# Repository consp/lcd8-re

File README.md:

# Gui based on lvgl9 for eBikes using a VESC motor controller 

Features:
* customisable (obviously ...)
* Faster update rates than any factory device
* Uses LVGL
* Has MCU with sufficient power and memory to do everything I want it to without too much problems.

## who is this for?

Anyone who wants to build their own eBike display and wants an example. This project is provided as is. No commercial usage is allowed of any kind unless stated explicitly otherwise.

### Who is this not for?

Anyone who expects a ready made product without effort.

## Supported platforms 

- Custom display:
  - Transflective LCD
  - 4 button support
  - Persistent Real time clock (if battery added) 
  - CAN/UART capable
  - Fast
  - Be able to connect to phone to show nav updates (via custom [gadgetbridge app](https://github.com/consp/Gadgetbridge))
  - Connect and use VESC messages ([custom version needed](https://github.com/consp/bldc), [custom tooling needed](https://github.com/consp/vesc-tool))
  - STM32H743
  - Should have enough power to output 1.5A on the 5V rail to USB

## Known issues
Probably many, there is a bug in the PCB making the ADC unreliable when a battery is installed.

# Attribution
Temperature icon: [Temperature Vectors by Vecteezy](https://www.vecteezy.com/free-vector/temperature)
Engine icon: [Heat icons created by HAJICON - Flaticon](https://www.flaticon.com/free-icons/heatv)
Brake icon: [Brake icons created by Smashicons - Flaticon](https://www.flaticon.com/free-icons/brake)
Trip icon: [Trip icons created by improstudio - Flaticon](https://www.flaticon.com/free-icons/trip)
Other icons: [Uicons - Flaticon](https://www.flaticon.com/uicons)
Headlight and headlight auto: [Headlight icons created by TravisAvery - Flaticon](https://www.flaticon.com/free-icon/headlights_9104236)

# License
All stuff not already licenced otherwise is only available under CC-BY-NC-4.0 https://creativecommons.org/licenses/by-nc/4.0/ . For commercial use contact me. No waranty of any kind is provided. No claims of any kind can be made.

# Contribution

If, for some reason, you want to add something or make a pull request: It's fine to do so but don't expect a prompt response. Any LLM based code or other generated files will be rejected without warning.
If, for some reason, you have a question: Use the discussion part of github. Do not expect a prompt response.

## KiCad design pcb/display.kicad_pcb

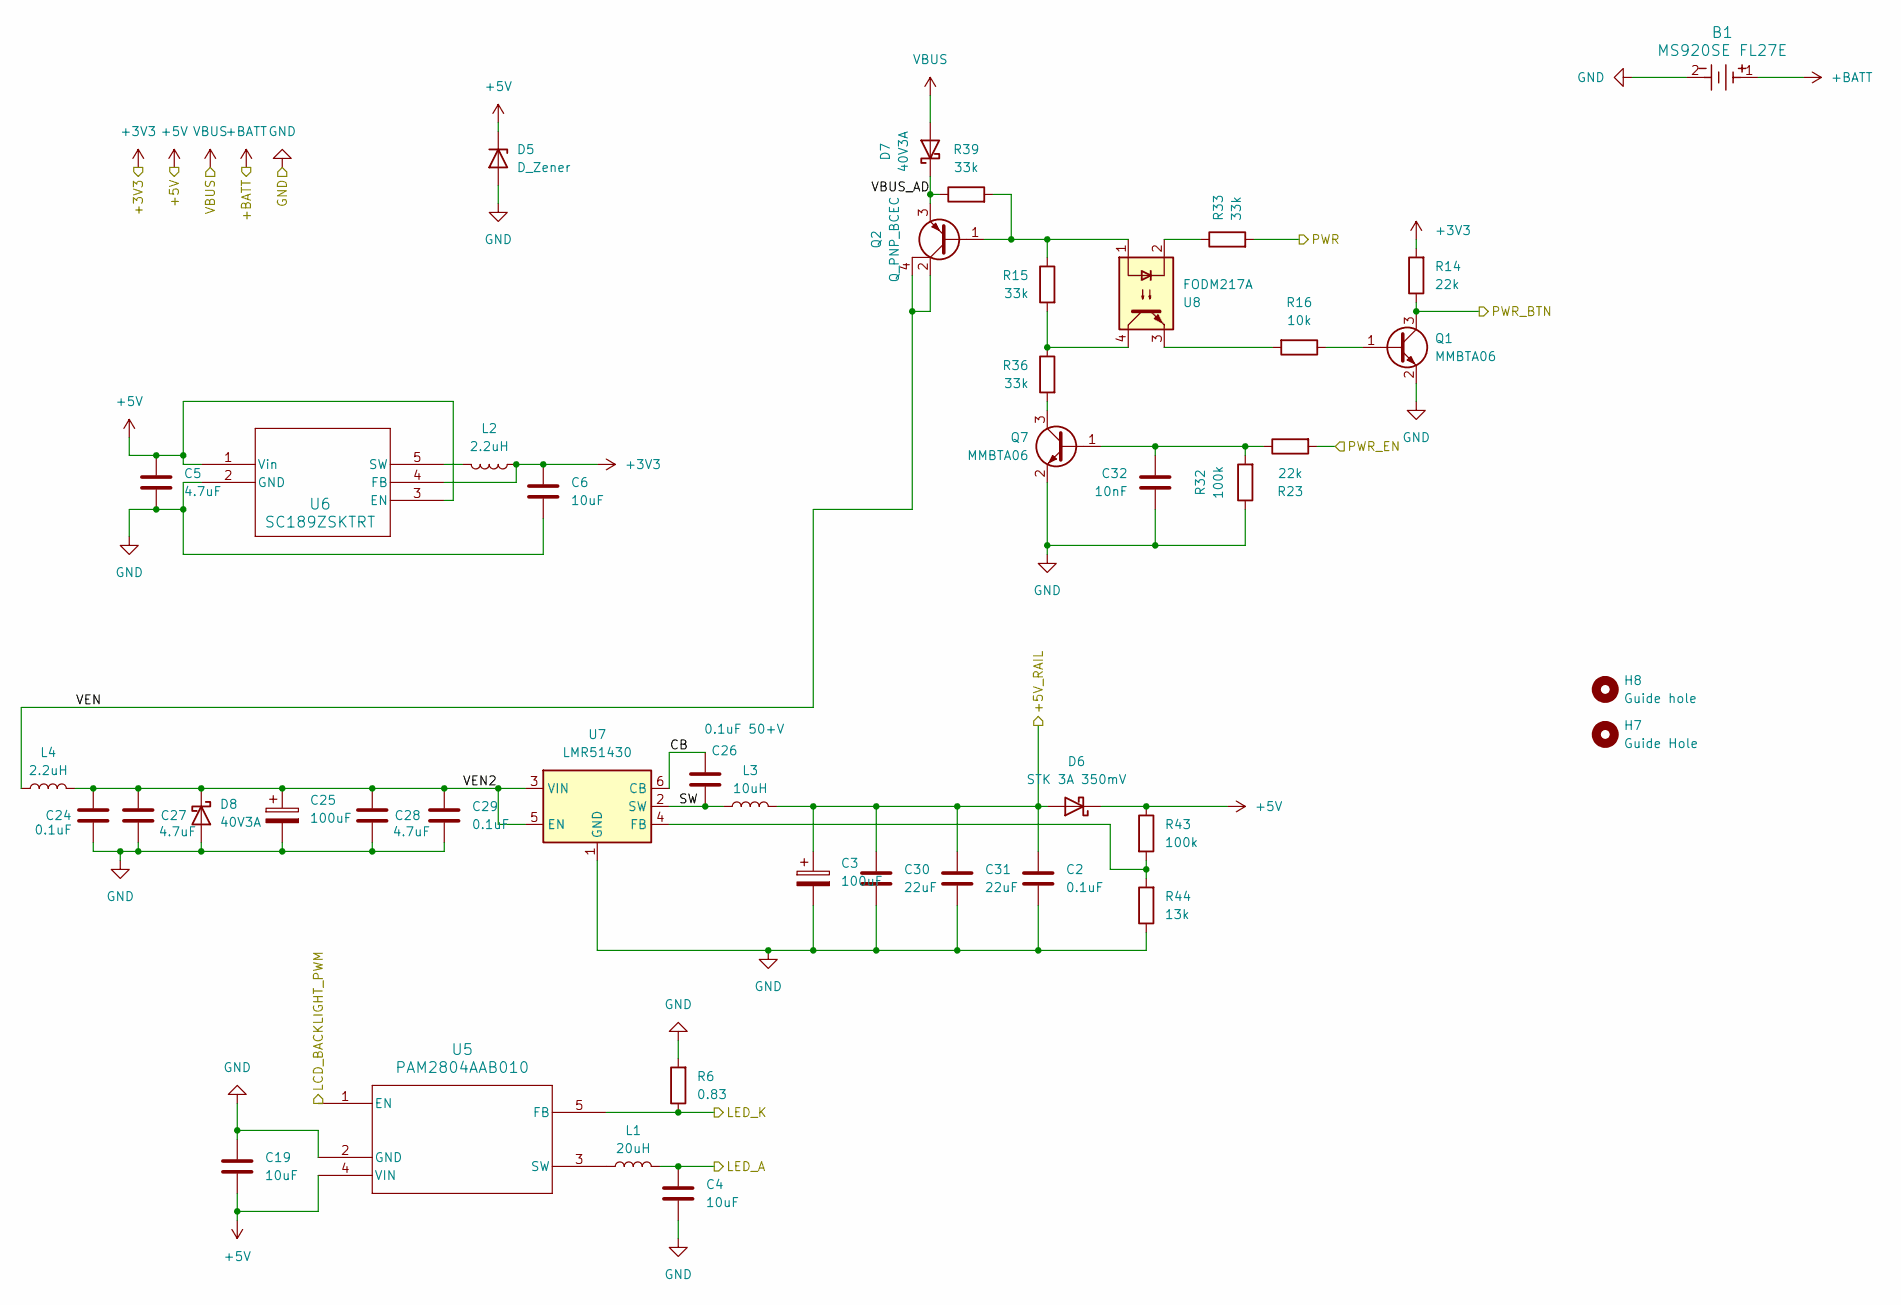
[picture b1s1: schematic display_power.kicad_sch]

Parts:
B1: MS920SE FL27E; BATT_MS920SE_FL27E_SEI
C2: 0.1uF; C_0805_2012Metric
C3, C25: 100uF; CP_Elec_10x10.5
C4, C6: 10uF; C_0805_2012Metric
C5: 4.7uF; C_0805_2012Metric
C19: 10uF; C_1206_3216Metric_Pad1.33x1.80mm_HandSolder
C24, C29: 0.1uF; C_0805_2012Metric_Pad1.18x1.45mm_HandSolder
C26: 0.1uF 50+V; C_0805_2012Metric_Pad1.18x1.45mm_HandSolder
C27, C28: 4.7uF; C_0805_2012Metric_Pad1.18x1.45mm_HandSolder
C30, C31: 22uF; C_0805_2012Metric_Pad1.18x1.45mm_HandSolder
C32: 10nF; C_0805_2012Metric
D5: D_Zener; D_SOD-323_HandSoldering
D6: STK 3A 350mV; D_SOD-128
D7: 40V3A; D_SOD-128
D8: 40V3A; D_SOD-123
H7: Guide Hole; ToolingHole_1.152mm
H8: Guide hole; ToolingHole_1.152mm
L1: 20uH; L_Taiyo-Yuden_NR-50xx_HandSoldering
L2: 2.2uH; L_Taiyo-Yuden_NR-20xx_HandSoldering
L3: 10uH; L_Bourns_SRP1038C_10.0x10.0mm
L4: 2.2uH; L_Taiyo-Yuden_NR-50xx_HandSoldering
Q1, Q7: MMBTA06; SOT-23
Q2: Q_PNP_BCEC; SOT-223-3_TabPin2
R6: 0.83; R_0805_2012Metric_Pad1.20x1.40mm_HandSolder
R14, R23: 22k; R_0805_2012Metric_Pad1.20x1.40mm_HandSolder
R15, R33, R36, R39: 33k; R_0805_2012Metric_Pad1.20x1.40mm_HandSolder
R16: 10k; R_0805_2012Metric_Pad1.20x1.40mm_HandSolder
R32, R43: 100k; R_0805_2012Metric_Pad1.20x1.40mm_HandSolder
R44: 13k; R_0805_2012Metric_Pad1.20x1.40mm_HandSolder
U5: PAM2804AAB010; PAM2804_DIO
U6: SC189ZSKTRT; MF05A_TEX
U7: LMR51430; SOT-23-6
U8: FODM217A; SOP-4_4.4x2.6mm_P1.27mm

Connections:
+3V3: C6.1, L2.1, R14.2, U6.4 (FB); also elsewhere on the board
+5V: C5.1, C19.2, D5.1 (K), D6.1 (K), R43.1, U5.4 (VIN), U6.1 (Vin), U6.3 (EN); also elsewhere on the board
+BATT: B1.1; also elsewhere on the board
/Connectors/LED_A: C4.1, L1.2; also elsewhere on the board
/Connectors/LED_K: R6.1, U5.5 (FB); also elsewhere on the board
/Connectors/PWR: R33.2; also elsewhere on the board
/MCU/LCD_BACKLIGHT_PWM: U5.1 (EN); also elsewhere on the board
/MCU/PWR_BTN: Q1.3 (C), R14.1; also elsewhere on the board
/MCU/PWR_EN: R23.2; also elsewhere on the board
/Other/+5V_RAIL: C2.1, C3.1, C30.1, C31.1, D6.2 (A), L3.2; also elsewhere on the board
/Power/CB: C26.1, U7.6 (CB)
/Power/SW: C26.2, L3.1, U7.2 (SW)
/Power/VBUS_AD: D7.1 (K), Q2.3 (E), R39.1
/Power/VEN: L4.1, Q2.2 (C), Q2.4 (C)
/Power/VEN2: C24.1, C25.1, C27.1, C28.1, C29.1, D8.1 (K), L4.2, U7.3 (VIN), U7.5 (EN)
GND: B1.2, C2.2, C3.2, C4.2, C5.2, C6.2, C19.1, C24.2, C25.2, C27.2, C28.2, C29.2, C30.2, C31.2, C32.2, D5.2 (A), D8.2 (A), Q1.2 (E), Q7.2 (E), R6.2, R32.1, R44.1, U5.2 (GND), U6.2 (GND), U7.1 (GND); also elsewhere on the board
unnamed: Q1.1 (B), R16.1
unnamed: Q2.1 (B), R15.1, R39.2, U8.1
unnamed: C32.1, Q7.1 (B), R23.1, R32.2
unnamed: Q7.3 (C), R36.2
unnamed: R15.2, R36.1, U8.4
unnamed: R16.2, U8.3
unnamed: R33.1, U8.2
unnamed: L1.1, U5.3 (SW)
unnamed: L2.2, U6.5 (SW)
unnamed: R43.2, R44.2, U7.4 (FB)
VBUS: D7.2 (A); also elsewhere on the board

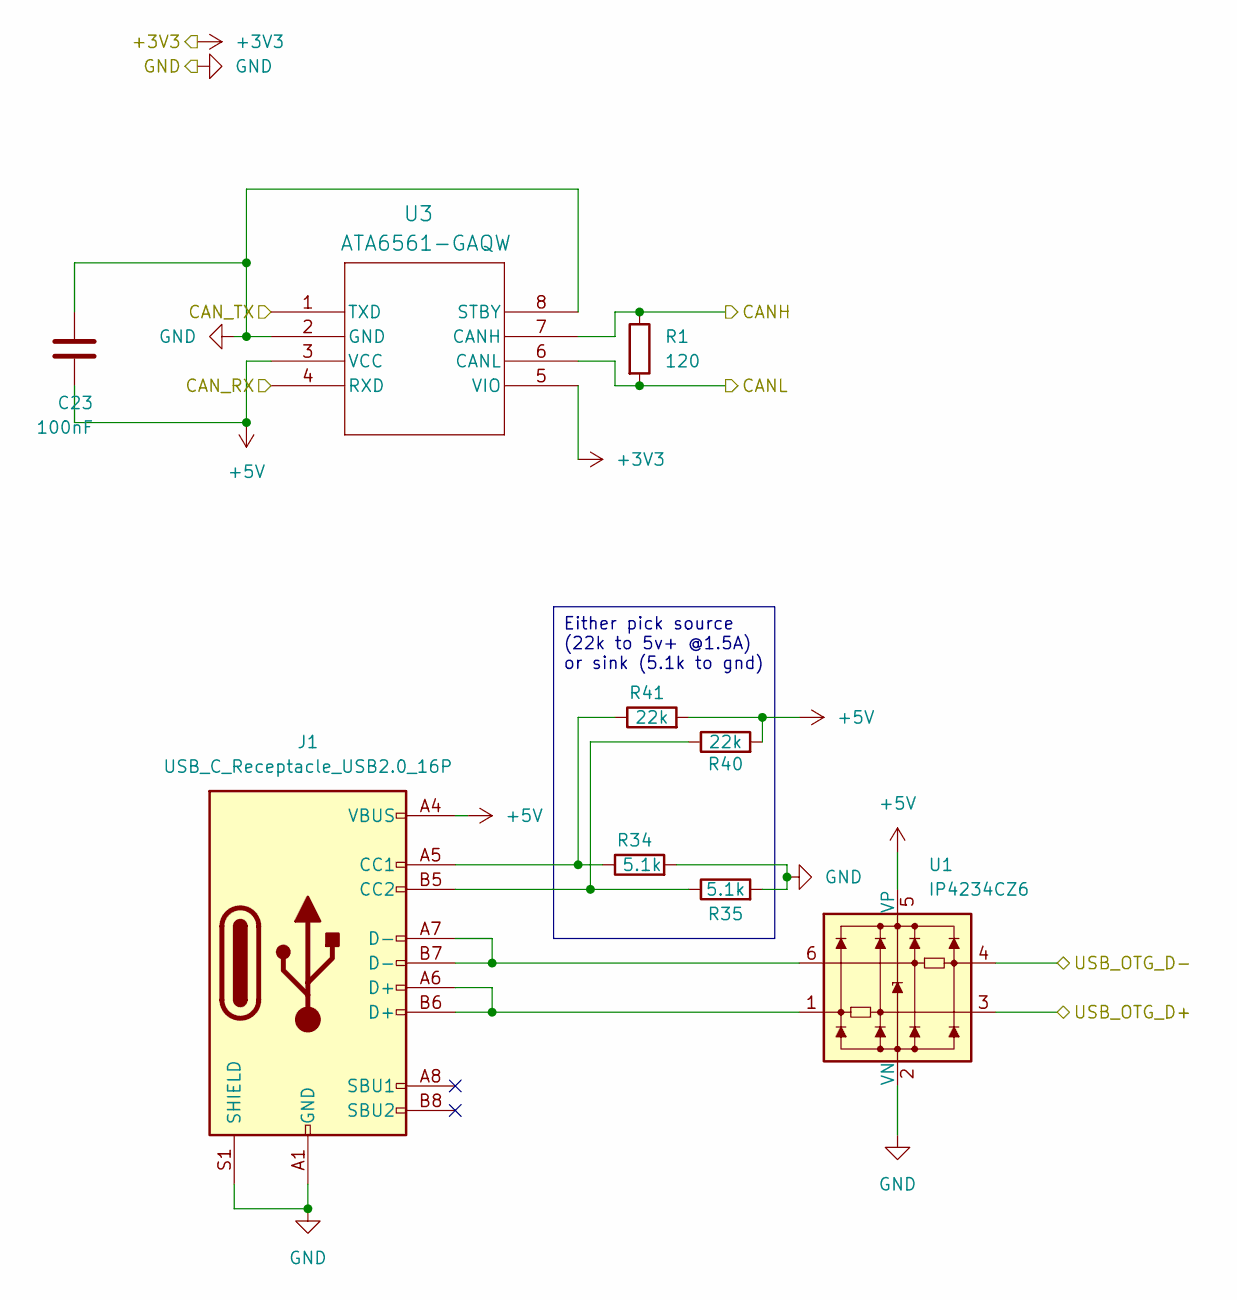
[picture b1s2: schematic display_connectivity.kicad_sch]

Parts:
C23: 100nF; C_0805_2012Metric
J1: USB_C_Receptacle_USB2.0_16P; USB_C_Receptacle_GCT_USB4085
R1: 120; R_0805_2012Metric_Pad1.20x1.40mm_HandSolder
R34, R35: 5.1k; R_0805_2012Metric
R40, R41: 22k; R_0805_2012Metric
U1: IP4234CZ6; SC-74-6_1.55x2.9mm_P0.95mm
U3: ATA6561-GAQW; SOIC8_4P9X3P9MC_MCH

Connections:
+3V3: U3.5 (VIO); also elsewhere on the board
+5V: C23.1, J1.A4 (VBUS), J1.A9 (VBUS), J1.B4 (VBUS), J1.B9 (VBUS), R40.2, R41.2, U1.5 (VP), U3.3 (VCC); also elsewhere on the board
/Connectivity/CANH: R1.1, U3.7 (CANH); also elsewhere on the board
/Connectivity/CANL: R1.2, U3.6 (CANL); also elsewhere on the board
/Connectivity/CAN_RX: U3.4 (RXD); also elsewhere on the board
/Connectivity/CAN_TX: U3.1 (TXD); also elsewhere on the board
/Connectivity/USB_OTG_D+: U1.3; also elsewhere on the board
/Connectivity/USB_OTG_D-: U1.4; also elsewhere on the board
GND: C23.2, J1.A1 (GND), J1.A12 (GND), J1.B1 (GND), J1.B12 (GND), J1.S1 (SHIELD), R34.2, R35.2, U1.2 (VN), U3.2 (GND), U3.8 (STBY); also elsewhere on the board
unnamed: J1.A5 (CC1), R34.1, R41.1
unnamed: J1.B5 (CC2), R35.1, R40.1
unnamed: J1.A6 (D+), J1.B6 (D+), U1.1
unnamed: J1.A7 (D-), J1.B7 (D-), U1.6

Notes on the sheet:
Either pick source (22k to 5v+ @1.5A) or sink (5.1k to gnd)

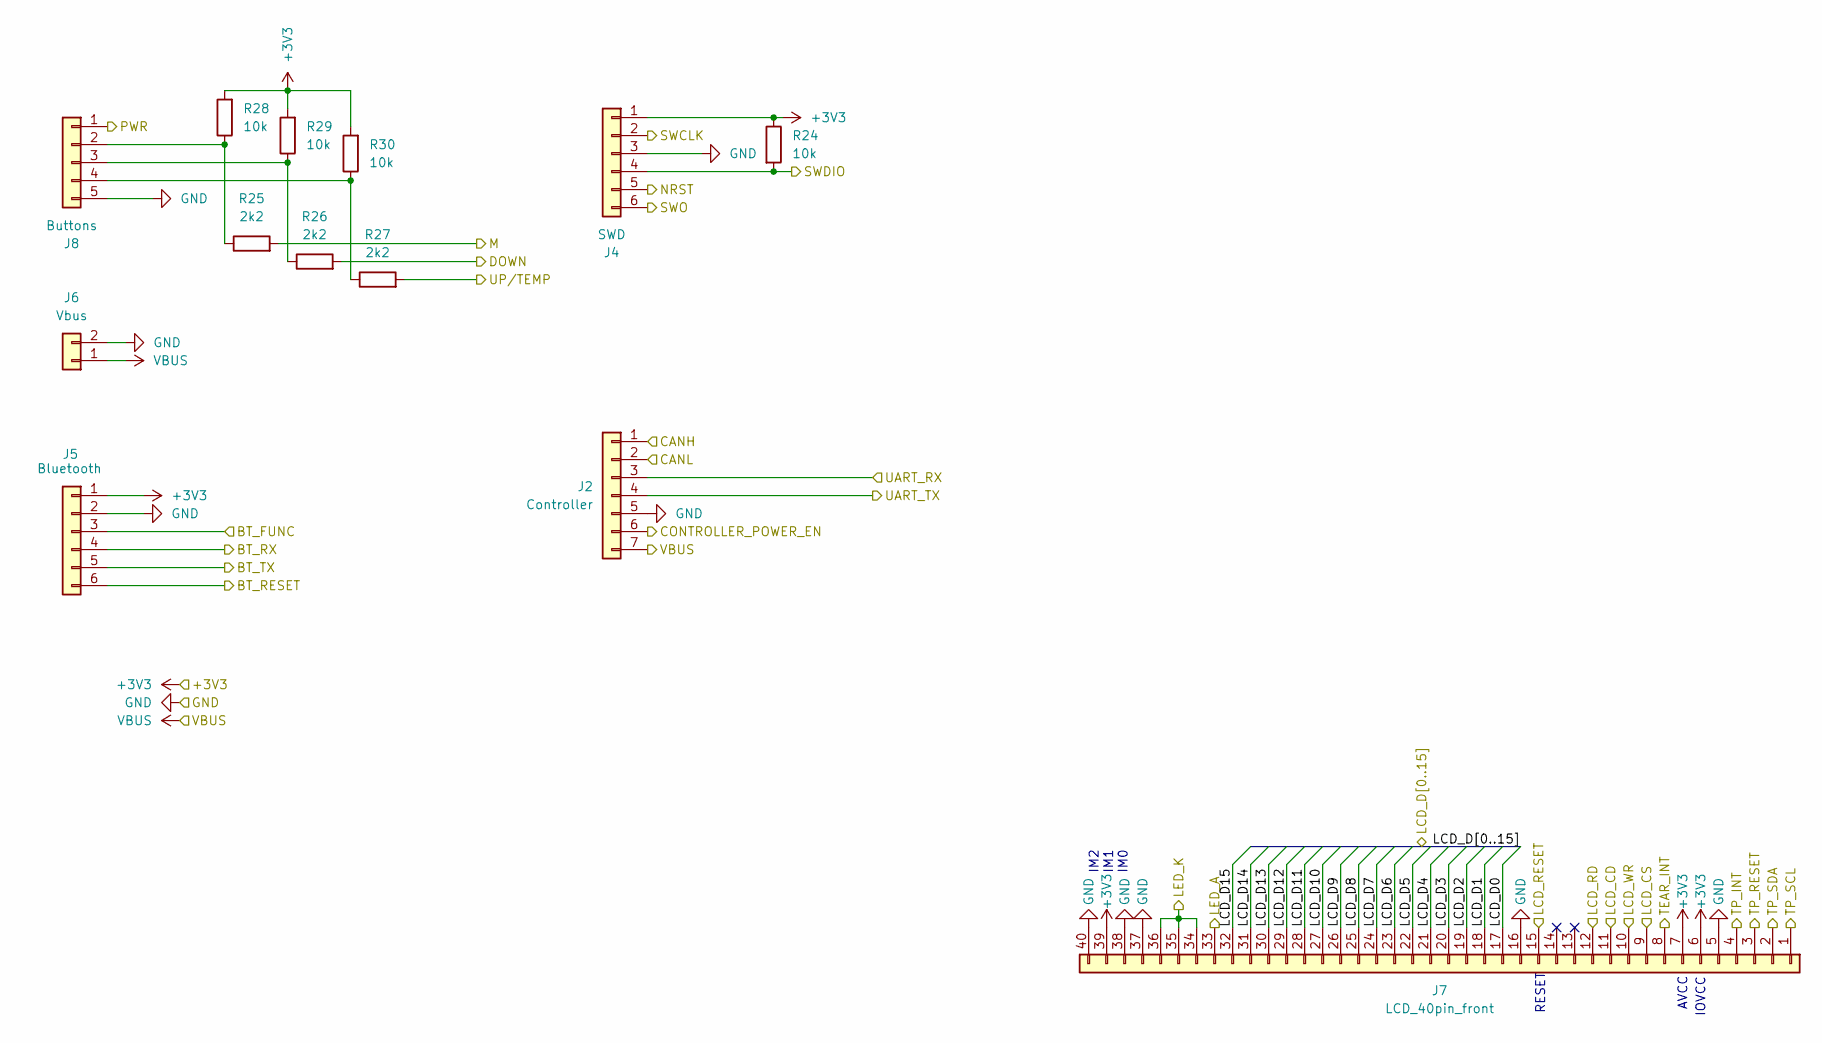
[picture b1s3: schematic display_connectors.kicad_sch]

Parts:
J2: Controller; JST_XH_B7B-XH-A_1x07_P2.50mm_Vertical
J4: SWD; JST_PH_B6B-PH-K_1x06_P2.00mm_Vertical
J5: Bluetooth; JST_XH_B6B-XH-A_1x06_P2.50mm_Vertical
J6: Vbus; JST_XH_B2B-XH-A_1x02_P2.50mm_Vertical
J7: LCD_40pin_front; Hirose_FH12-40S-0.5SH_1x40-1MP_P0.50mm_Horizontal
J8: Buttons; JST_XH_B5B-XH-A_1x05_P2.50mm_Vertical
R24, R28, R29, R30: 10k; R_0805_2012Metric_Pad1.20x1.40mm_HandSolder
R25, R26, R27: 2k2; R_0805_2012Metric_Pad1.20x1.40mm_HandSolder

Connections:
+3V3: J4.1, J5.1, J7.6, J7.7, J7.39, R24.1, R28.2, R29.2, R30.2; also elsewhere on the board
/Connectivity/CANH: J2.1; also elsewhere on the board
/Connectivity/CANL: J2.2; also elsewhere on the board
/Connectors/BT_FUNC: J5.3; also elsewhere on the board
/Connectors/BT_RESET: J5.6; also elsewhere on the board
/Connectors/BT_RX: J5.4; also elsewhere on the board
/Connectors/BT_TX: J5.5; also elsewhere on the board
/Connectors/CONTROLLER_POWER_EN: J2.6; also elsewhere on the board
/Connectors/LCD_CS: J7.9; also elsewhere on the board
/Connectors/LCD_D0: J7.17; also elsewhere on the board
/Connectors/LCD_D1: J7.18; also elsewhere on the board
/Connectors/LCD_D2: J7.19; also elsewhere on the board
/Connectors/LCD_D3: J7.20; also elsewhere on the board
/Connectors/LCD_D4: J7.21; also elsewhere on the board
/Connectors/LCD_D5: J7.22; also elsewhere on the board
/Connectors/LCD_D6: J7.23; also elsewhere on the board
/Connectors/LCD_D7: J7.24; also elsewhere on the board
/Connectors/LCD_D8: J7.25; also elsewhere on the board
/Connectors/LCD_D9: J7.26; also elsewhere on the board
/Connectors/LCD_D10: J7.27; also elsewhere on the board
/Connectors/LCD_D11: J7.28; also elsewhere on the board
/Connectors/LCD_D12: J7.29; also elsewhere on the board
/Connectors/LCD_D13: J7.30; also elsewhere on the board
/Connectors/LCD_D14: J7.31; also elsewhere on the board
/Connectors/LCD_D15: J7.32; also elsewhere on the board
/Connectors/LED_A: J7.33; also elsewhere on the board
/Connectors/LED_K: J7.34, J7.35, J7.36; also elsewhere on the board
/Connectors/PWR: J8.1; also elsewhere on the board
/Connectors/SWCLK: J4.2; also elsewhere on the board
/Connectors/SWDIO: J4.4, R24.2; also elsewhere on the board
/Connectors/SWO: J4.6; also elsewhere on the board
/Connectors/TEAR_INT: J7.8; also elsewhere on the board
/Connectors/TP_INT: J7.4; also elsewhere on the board
/Connectors/TP_RESET: J7.3; also elsewhere on the board
/Connectors/TP_SCL: J7.1; also elsewhere on the board
/Connectors/TP_SDA: J7.2; also elsewhere on the board
/Connectors/UART_RX: J2.3; also elsewhere on the board
/Connectors/UART_TX: J2.4; also elsewhere on the board
/MCU/DOWN: R26.2; also elsewhere on the board
/MCU/LCD_CD: J7.11; also elsewhere on the board
/MCU/LCD_RD: J7.12; also elsewhere on the board
/MCU/LCD_WR: J7.10; also elsewhere on the board
/MCU/M: R25.2; also elsewhere on the board
/MCU/NRST: J4.5, J7.15; also elsewhere on the board
/MCU/UP/TEMP: R27.2; also elsewhere on the board
GND: J2.5, J4.3, J5.2, J6.2, J7.5, J7.16, J7.37, J7.38, J7.40, J8.5; also elsewhere on the board
unnamed: J8.2, R25.1, R28.1
unnamed: J8.3, R26.1, R29.1
unnamed: J8.4, R27.1, R30.1
VBUS: J2.7, J6.1; also elsewhere on the board

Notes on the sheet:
AVCC
RESET
IOVCC
IM2 IM1 IM0

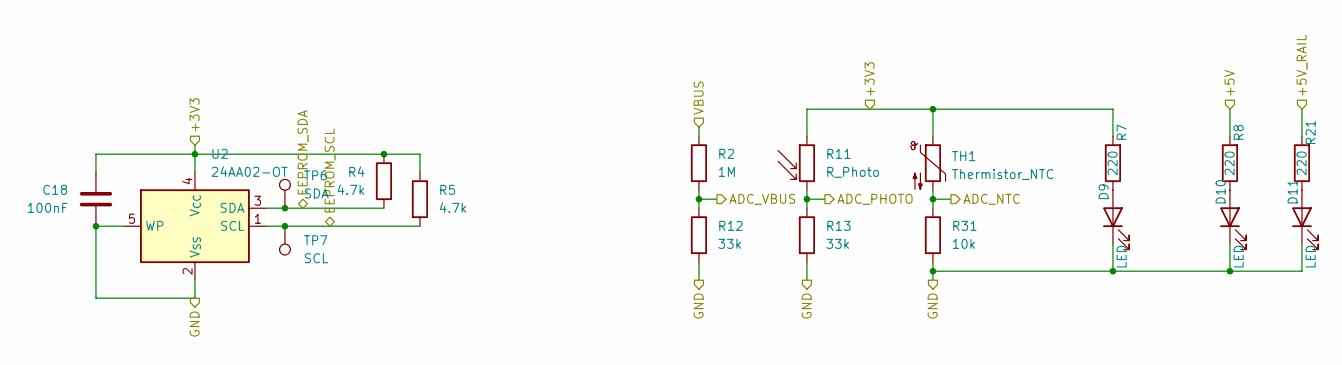
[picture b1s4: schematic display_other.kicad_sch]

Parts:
C18: 100nF; C_0805_2012Metric
D9, D10, D11: LED; LED_0805_2012Metric_Pad1.15x1.40mm_HandSolder
R2: 1M; R_0805_2012Metric_Pad1.20x1.40mm_HandSolder
R4, R5: 4.7k; R_0805_2012Metric_Pad1.20x1.40mm_HandSolder
R7, R8, R21: 220; R_0805_2012Metric_Pad1.20x1.40mm_HandSolder
R11: R_Photo; R_LDR_5.1x4.3mm_P3.4mm_Vertical
R12, R13: 33k; R_0805_2012Metric_Pad1.20x1.40mm_HandSolder
R31: 10k; R_0805_2012Metric_Pad1.20x1.40mm_HandSolder
TH1: Thermistor_NTC; R_0805_2012Metric_Pad1.20x1.40mm_HandSolder
TP6: SDA; TestPoint_Pad_D1.5mm
TP7: SCL; TestPoint_Pad_D1.5mm
U2: 24AA02-OT; SOT-23-5

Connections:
+3V3: C18.2, R4.1, R5.1, R7.2, R11.1, TH1.1, U2.4 (V_{CC}); also elsewhere on the board
+5V: R8.2; also elsewhere on the board
/MCU/ADC_NTC: R31.1, TH1.2; also elsewhere on the board
/MCU/ADC_VBUS: R2.2, R12.1; also elsewhere on the board
/MCU/ADH_PHOTO: R11.2, R13.1; also elsewhere on the board
/MCU/EEPROM_SCA: R4.2, TP6.1, U2.3 (SDA); also elsewhere on the board
/MCU/EEPROM_SCL: R5.2, TP7.1, U2.1 (SCL); also elsewhere on the board
/Other/+5V_RAIL: R21.2; also elsewhere on the board
GND: C18.1, D9.1 (K), D10.1 (K), D11.1 (K), R12.2, R13.2, R31.2, U2.2 (V_{SS}), U2.5 (WP); also elsewhere on the board
unnamed: D9.2 (A), R7.1
unnamed: D10.2 (A), R8.1
unnamed: D11.2 (A), R21.1
VBUS: R2.1; also elsewhere on the board

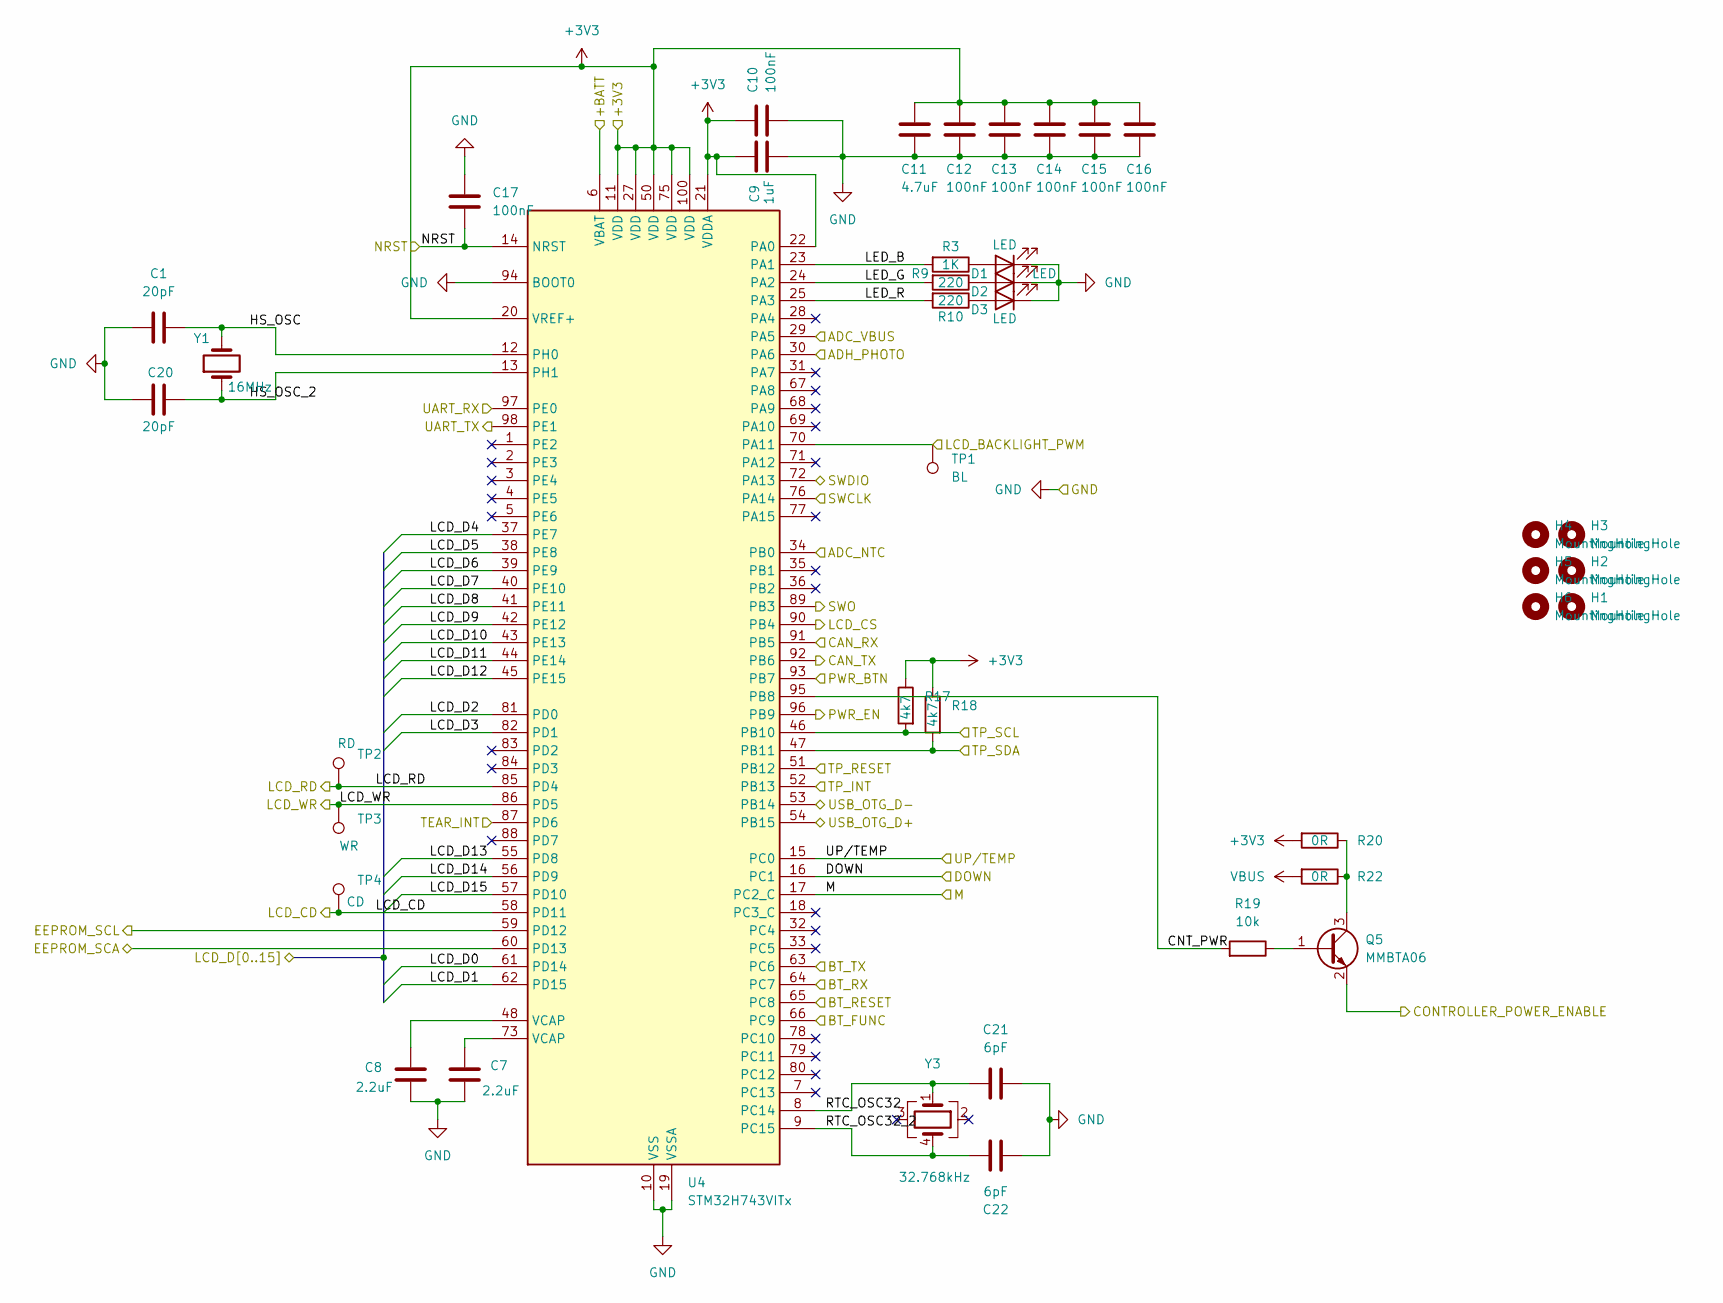
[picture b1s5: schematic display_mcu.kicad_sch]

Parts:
C1: 20pF; C_0805_2012Metric
C7, C8: 2.2uF; C_0805_2012Metric
C9: 1uF; C_0805_2012Metric
C10, C12, C13, C14, C15, C16, C17: 100nF; C_0805_2012Metric
C11: 4.7uF; C_0805_2012Metric
C20: 20pF; C_0805_2012Metric_Pad1.18x1.45mm_HandSolder
C21, C22: 6pF; C_0805_2012Metric_Pad1.18x1.45mm_HandSolder
D1, D2, D3: LED; LED_0805_2012Metric_Pad1.15x1.40mm_HandSolder
H1, H2, H3, H4, H5, H6: MountingHole; MountingHole_2.2mm_M2
Q5: MMBTA06; SOT-23
R3: 1K; R_0805_2012Metric_Pad1.20x1.40mm_HandSolder
R9, R10: 220; R_0805_2012Metric_Pad1.20x1.40mm_HandSolder
R17, R18: 4k7; R_0805_2012Metric_Pad1.20x1.40mm_HandSolder
R19: 10k; R_0805_2012Metric_Pad1.20x1.40mm_HandSolder
R20, R22: 0R; R_0805_2012Metric_Pad1.20x1.40mm_HandSolder
TP1: BL; TestPoint_Pad_D1.5mm
TP2: RD; TestPoint_Pad_D1.5mm
TP3: WR; TestPoint_Pad_D1.5mm
TP4: CD; TestPoint_Pad_D1.5mm
U4: STM32H743VITx; LQFP-100_14x14mm_P0.5mm
Y1: 16MHz; Crystal_SMD_HC49-SD
Y3: 32.768kHz; Crystal_SMD_Abracon_ABS25-4Pin_8.0x3.8mm

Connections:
+3V3: C9.1, C10.1, C11.2, C12.2, C13.2, C14.2, C15.2, C16.2, R17.1, R18.1, R20.2, U4.11 (VDD), U4.20 (VREF+), U4.21 (VDDA), U4.22 (PA0), U4.27 (VDD), U4.50 (VDD), U4.75 (VDD), U4.100 (VDD); also elsewhere on the board
+BATT: U4.6 (VBAT); also elsewhere on the board
/Connectivity/CAN_RX: U4.91 (PB5); also elsewhere on the board
/Connectivity/CAN_TX: U4.92 (PB6); also elsewhere on the board
/Connectivity/USB_OTG_D+: U4.54 (PB15); also elsewhere on the board
/Connectivity/USB_OTG_D-: U4.53 (PB14); also elsewhere on the board
/Connectors/BT_FUNC: U4.66 (PC9); also elsewhere on the board
/Connectors/BT_RESET: U4.65 (PC8); also elsewhere on the board
/Connectors/BT_RX: U4.64 (PC7); also elsewhere on the board
/Connectors/BT_TX: U4.63 (PC6); also elsewhere on the board
/Connectors/CONTROLLER_POWER_EN: Q5.2 (E); also elsewhere on the board
/Connectors/LCD_CS: U4.90 (PB4); also elsewhere on the board
/Connectors/LCD_D0: U4.61 (PD14); also elsewhere on the board
/Connectors/LCD_D1: U4.62 (PD15); also elsewhere on the board
/Connectors/LCD_D2: U4.81 (PD0); also elsewhere on the board
/Connectors/LCD_D3: U4.82 (PD1); also elsewhere on the board
/Connectors/LCD_D4: U4.37 (PE7); also elsewhere on the board
/Connectors/LCD_D5: U4.38 (PE8); also elsewhere on the board
/Connectors/LCD_D6: U4.39 (PE9); also elsewhere on the board
/Connectors/LCD_D7: U4.40 (PE10); also elsewhere on the board
/Connectors/LCD_D8: U4.41 (PE11); also elsewhere on the board
/Connectors/LCD_D9: U4.42 (PE12); also elsewhere on the board
/Connectors/LCD_D10: U4.43 (PE13); also elsewhere on the board
/Connectors/LCD_D11: U4.44 (PE14); also elsewhere on the board
/Connectors/LCD_D12: U4.45 (PE15); also elsewhere on the board
/Connectors/LCD_D13: U4.55 (PD8); also elsewhere on the board
/Connectors/LCD_D14: U4.56 (PD9); also elsewhere on the board
/Connectors/LCD_D15: U4.57 (PD10); also elsewhere on the board
/Connectors/SWCLK: U4.76 (PA14); also elsewhere on the board
/Connectors/SWDIO: U4.72 (PA13); also elsewhere on the board
/Connectors/SWO: U4.89 (PB3); also elsewhere on the board
/Connectors/TEAR_INT: U4.87 (PD6); also elsewhere on the board
/Connectors/TP_INT: U4.52 (PB13); also elsewhere on the board
/Connectors/TP_RESET: U4.51 (PB12); also elsewhere on the board
/Connectors/TP_SCL: R17.2, U4.46 (PB10); also elsewhere on the board
/Connectors/TP_SDA: R18.2, U4.47 (PB11); also elsewhere on the board
/Connectors/UART_RX: U4.97 (PE0); also elsewhere on the board
/Connectors/UART_TX: U4.98 (PE1); also elsewhere on the board
/MCU/ADC_NTC: U4.34 (PB0); also elsewhere on the board
/MCU/ADC_VBUS: U4.29 (PA5); also elsewhere on the board
/MCU/ADH_PHOTO: U4.30 (PA6); also elsewhere on the board
/MCU/CNT_PWR: R19.2, U4.95 (PB8)
/MCU/DOWN: U4.16 (PC1); also elsewhere on the board
/MCU/EEPROM_SCA: U4.60 (PD13); also elsewhere on the board
/MCU/EEPROM_SCL: U4.59 (PD12); also elsewhere on the board
/MCU/HS_OSC: C1.1, U4.12 (PH0), Y1.2
/MCU/HS_OSC_2: C20.2, U4.13 (PH1), Y1.1
/MCU/LCD_BACKLIGHT_PWM: TP1.1, U4.70 (PA11); also elsewhere on the board
/MCU/LCD_CD: TP4.1, U4.58 (PD11); also elsewhere on the board
/MCU/LCD_RD: TP2.1, U4.85 (PD4); also elsewhere on the board
/MCU/LCD_WR: TP3.1, U4.86 (PD5); also elsewhere on the board
/MCU/LED_B: R3.2, U4.23 (PA1)
/MCU/LED_G: R9.2, U4.24 (PA2)
/MCU/LED_R: R10.2, U4.25 (PA3)
/MCU/M: U4.17 (PC2_C); also elsewhere on the board
/MCU/NRST: C17.2, U4.14 (NRST); also elsewhere on the board
/MCU/PWR_BTN: U4.93 (PB7); also elsewhere on the board
/MCU/PWR_EN: U4.96 (PB9); also elsewhere on the board
/MCU/RTC_OSC32: C21.1, U4.8 (PC14), Y3.1
/MCU/RTC_OSC32_2: C22.2, U4.9 (PC15), Y3.4
/MCU/UP/TEMP: U4.15 (PC0); also elsewhere on the board
GND: C1.2, C7.2, C8.2, C9.2, C10.2, C11.1, C12.1, C13.1, C14.1, C15.1, C16.1, C17.1, C20.1, C21.2, C22.1, D1.1 (K), D2.1 (K), D3.1 (K), U4.10 (VSS), U4.19 (VSSA), U4.26 (VSS), U4.49 (VSS), U4.74 (VSS), U4.94 (BOOT0), U4.99 (VSS); also elsewhere on the board
unnamed: C7.1, U4.73 (VCAP)
unnamed: C8.1, U4.48 (VCAP)
unnamed: D1.2 (A), R3.1
unnamed: D2.2 (A), R9.1
unnamed: D3.2 (A), R10.1
unnamed: Q5.1 (B), R19.1
unnamed: Q5.3 (C), R20.1, R22.1
VBUS: R22.2; also elsewhere on the board

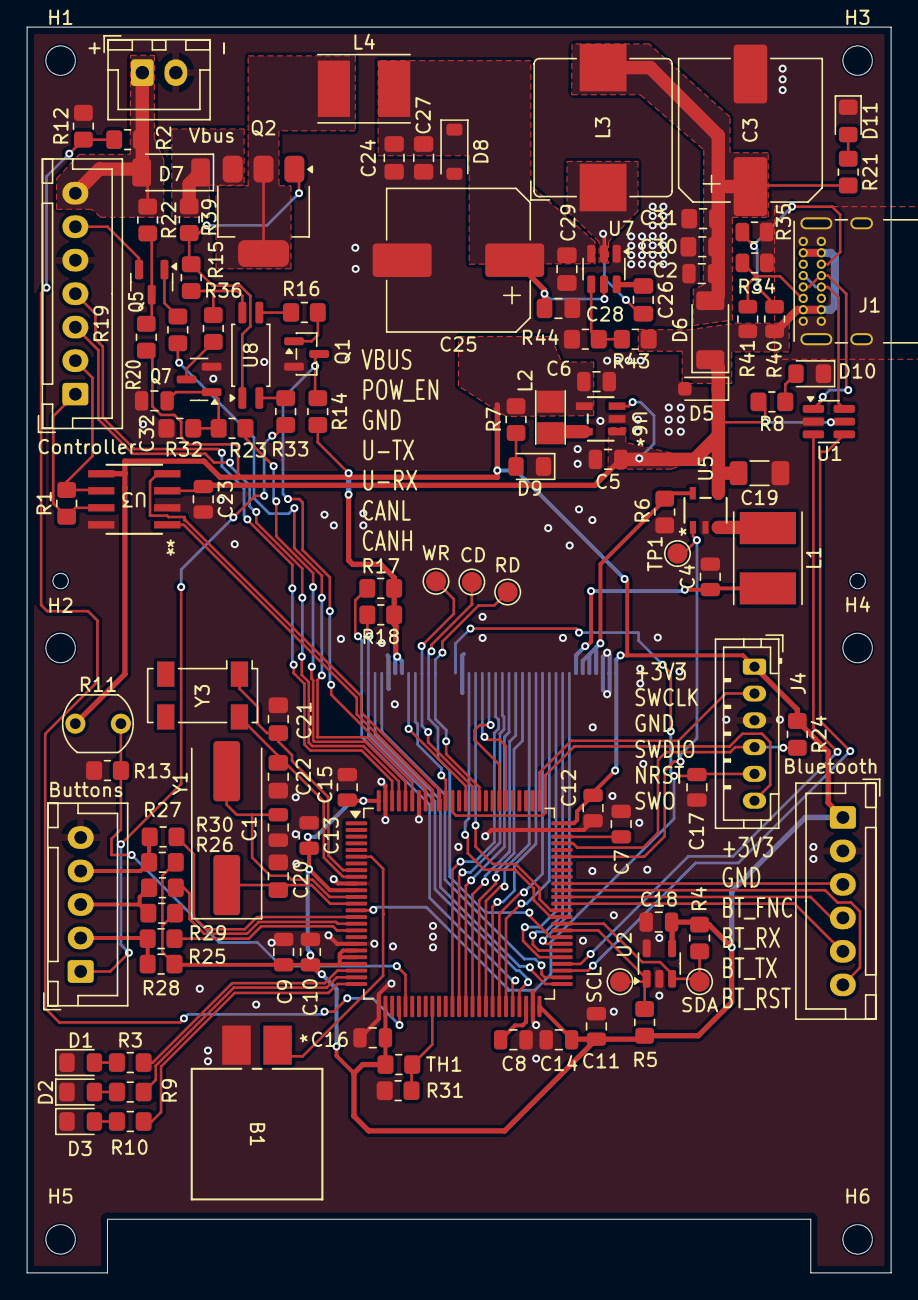
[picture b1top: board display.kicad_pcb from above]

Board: 2 copper layers, 64.5 x 93.0 mm, 124 parts (1 on the bottom side), 102 nets.

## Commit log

2025-02-21 Fix images
2025-02-21 Textual fixes
2025-02-22 Fixed wrong VDD/+5V lines
2025-02-23 Update README.md
    Changes to LCD data
2025-02-25 Update README.md
    Added eeprom and some display info
2025-03-05 Initial source commit, debug only, includes eeprom read/write and basic adc&button tooling. LCD does not function yet.
2025-03-05 Makefile
2025-03-05 Reference manual for at32f415 added
2025-03-05 ILI9488 documentation added
2025-03-05 lcd backlight with tim3 pwm
2025-03-07 Setup of sim and ugui
    * Note: 565 is broken in ugui, needs the changes to properly work e.g.
    with 8bit fonts
2025-03-11 Update README.md
    Added info about USB
2025-03-21 ugui basics working
2025-03-21 Switch to lvgl v8.4 and initial display
2025-04-03 Update README.md with A1013
2025-04-04 Version with almost everything working
2025-04-04 Working with custom EBICS fork, split hal
2025-04-16 Made ntc table constant
2025-04-16 Different filter settings for voltage and temperature
2025-04-16 Fix debug logging
2025-04-16 Added sim
2025-04-16 Working version, with DMA transfer option (a bit broken for now)
2025-04-16 Added submodule for lvgl
2025-04-16 Staging commit for new hal + new hal options
2025-04-16 More hal abastraction
2025-04-16 Basic dma working, but issues and broken eeprom i2c
2025-04-16 added missing files
2025-04-16 Communication via stdin/out for sim
2025-04-16 complete sim
2025-04-17 Some fixes to stuck updates and added controls in sim
2025-04-19 Added at32f435 as alternative cpu to allow lvgl 9 to work in the future
2025-04-19 Added flashhigh option to put most code in 0 cycle flash and data in the rest region for the at32f435
2025-04-19 Actually switch to 448k
2025-04-19 Sim fix
2025-05-17 Workingish at32f435
2025-05-25 Changed to less ram more sram flash and 8kb heap/stack
2025-05-25 Working VESC setup, removed default theme for space
2025-05-28 bugfixes, sim fixes and some minor changes
2025-05-30 Not final but close
2025-07-18 Start of own custom pcb and stm32h743 implementation with dma2d and 24/18bit color
2025-07-18 Redone dma2d/mdma/fmc flush, now proper 18bit
2026-06-11 Added missing images
2026-06-11 Changed default values for waiting for buttons at start
2026-06-11 Added fonts
2026-06-23 Added PCB files
2026-06-23 Update README.md attempt 2
2026-06-23 Saved pcb
2026-06-23 Added new images
2026-06-30 added correct urls to readme
